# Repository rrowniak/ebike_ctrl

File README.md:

# ebike_ctrl
A small but powerful on-board computer displaying main parameters of almost any electric bike.
It concists of three parts:
* Motherboard - sits close to the BLDC driver and battery. Main responsibility is to gather all needed data like battery voltage, temperatures, current, hall sensor output and so on. The motherboard communicates with UI module via CAN bus.
* Current sensor. This is a hardware module (no firmware needed) connected to the motherboard.
* UI - displays all valuable info to a user. It reads what the motherboard is sending via CAN bus, then interprets the data, does additional calculations and displays on EA DOGXL240W-7 (240x128 pixel COG LCD).

## Features

* Displays current up to +/- 100A, voltage up to 100V and battery percentage

* Current speed, distance traveled (three profiles)

* Consumption in Wh, Wh/km +gain from regenerative charging

* Temperatures: ambient, motor, battery, driver

* Allows for changing views

* and more

## Requirements and dependencies

* GNU Arm Embedded Toolchain

* [l_rr library](https://github.com/rrowniak/l_rr)

## License

Copyright (c) 2020 Rafal Rowniak rrowniak.com

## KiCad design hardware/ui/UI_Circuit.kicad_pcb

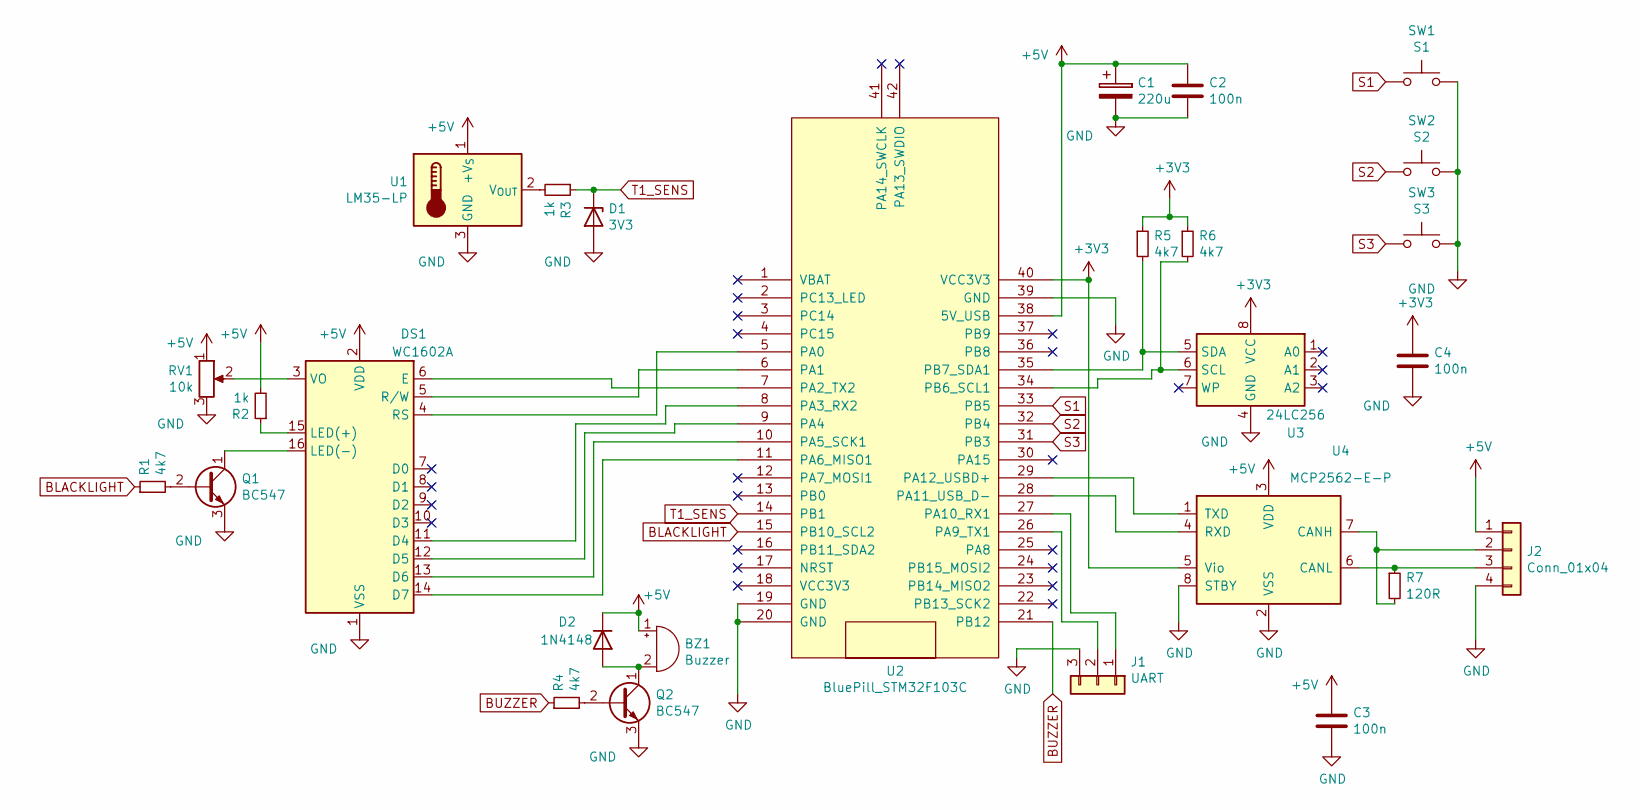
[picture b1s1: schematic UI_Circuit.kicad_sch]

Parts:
BZ1: Buzzer; Buzzer_15x7.5RM7.6
C1: 220u; CP_Radial_D10.0mm_P5.00mm
C2, C3, C4: 100n; C_1206_3216Metric
D1: 3V3; D_1206_3216Metric
D2: 1N4148; D_DO-35_SOD27_P7.62mm_Horizontal
DS1: WC1602A
J1: UART; PinHeader_1x03_P2.54mm_Vertical
J2: Conn_01x04; JST_EH_B4B-EH-A_1x04_P2.50mm_Vertical
Q1, Q2: BC547; TO-92_HandSolder
R1, R4, R5, R6: 4k7; R_1206_3216Metric
R2, R3: 1k; R_1206_3216Metric
R7: 120R; R_Axial_DIN0207_L6.3mm_D2.5mm_P10.16mm_Horizontal
RV1: 10k; Potentiometer_Piher_PT-6-V_Vertical
SW1: S1; SW_PUSH_6mm_H8mm
SW2: S2; SW_PUSH_6mm_H8mm
SW3: S3; SW_PUSH_6mm_H8mm
U1: LM35-LP; TO-92L_HandSolder
U2: BluePill_STM32F103C
U3: 24LC256; DIP-8_W7.62mm
U4: MCP2562-E-P; DIP-8_W7.62mm

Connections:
+3V3: C4.1, R5.1, R6.1, U2.40 (VCC3V3), U3.8 (VCC), U4.5 (Vio)
+5V: BZ1.1 (+), C1.1, C2.1, C3.1, D2.1 (K), DS1.2 (VDD), J2.1, R2.2, RV1.1, U1.1 (+V_{S}), U2.38 (5V_USB), U4.3 (VDD)
BLACKLIGHT: R1.1, U2.15 (PB10_SCL2)
BUZZER: R4.1, U2.21 (PB12)
GND: C1.2, C2.2, C3.2, C4.2, D1.2 (A), DS1.1 (VSS), J1.3, J2.4, Q1.3 (E), Q2.3 (E), RV1.3, SW1.2, SW2.2, SW3.2, U1.3 (GND), U2.19 (GND), U2.20 (GND), U2.39 (GND), U3.4 (GND), U4.2 (VSS), U4.8 (STBY)
unnamed: BZ1.2 (-), D2.2 (A), Q2.1 (C)
unnamed: DS1.3 (VO), RV1.2
unnamed: DS1.4 (RS), U2.5 (PA0)
unnamed: DS1.5 (R/W), U2.6 (PA1)
unnamed: DS1.6 (E), U2.7 (PA2_TX2)
unnamed: DS1.11 (D4), U2.8 (PA3_RX2)
unnamed: DS1.12 (D5), U2.9 (PA4)
unnamed: DS1.13 (D6), U2.10 (PA5_SCK1)
unnamed: DS1.14 (D7), U2.11 (PA6_MISO1)
unnamed: DS1.15 (LED(+)), R2.1
unnamed: DS1.16 (LED(-)), Q1.1 (C)
unnamed: J1.1, U2.27 (PA10_RX1)
unnamed: J1.2, U2.26 (PA9_TX1)
unnamed: J2.2, R7.2, U4.7 (CANH)
unnamed: J2.3, R7.1, U4.6 (CANL)
unnamed: Q1.2 (B), R1.2
unnamed: Q2.2 (B), R4.2
unnamed: R3.2, U1.2 (V_{OUT})
unnamed: R5.2, U2.35 (PB7_SDA1), U3.5 (SDA)
unnamed: R6.2, U2.34 (PB6_SCL1), U3.6 (SCL)
unnamed: U2.28 (PA11_USB_D-), U4.4 (RXD)
unnamed: U2.29 (PA12_USBD+), U4.1 (TXD)
S1: SW1.1, U2.33 (PB5)
S2: SW2.1, U2.32 (PB4)
S3: SW3.1, U2.31 (PB3)
T1_SENS: D1.1 (K), R3.1, U2.14 (PB1)

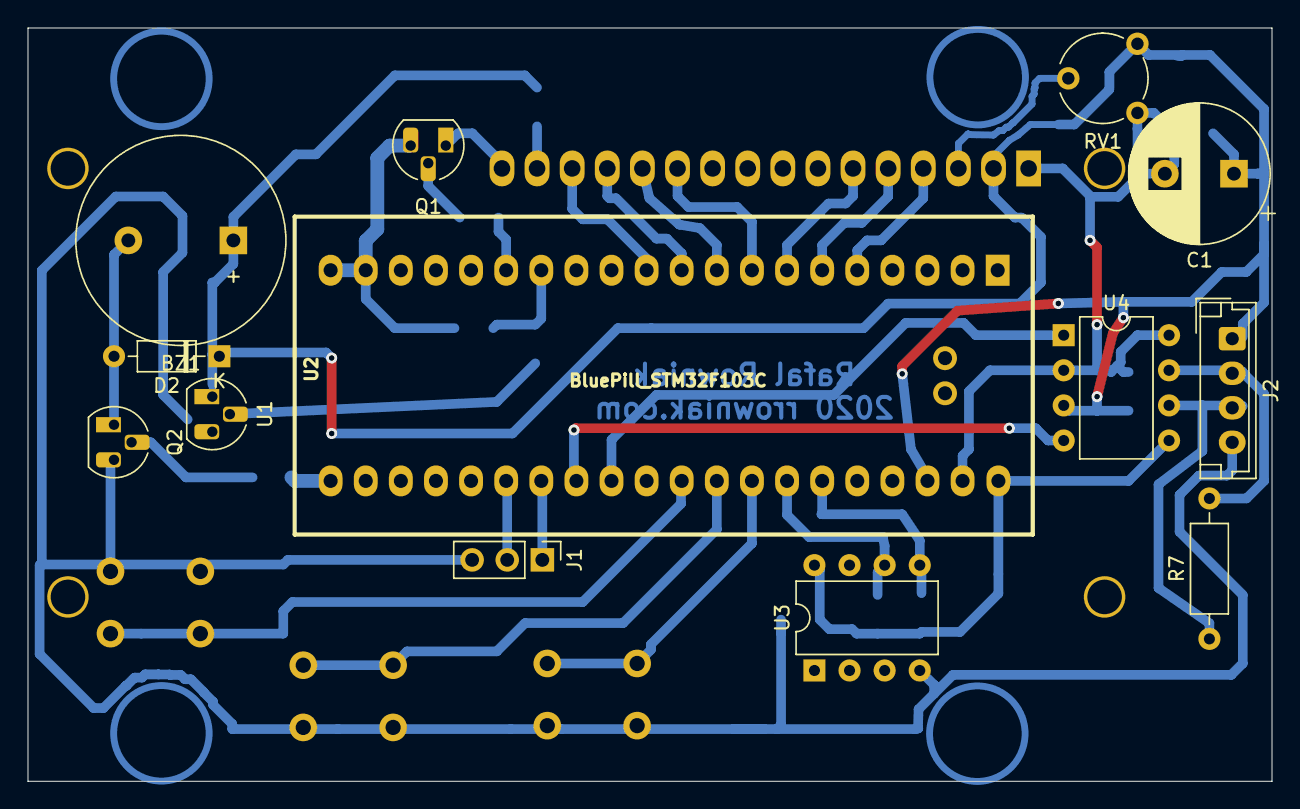
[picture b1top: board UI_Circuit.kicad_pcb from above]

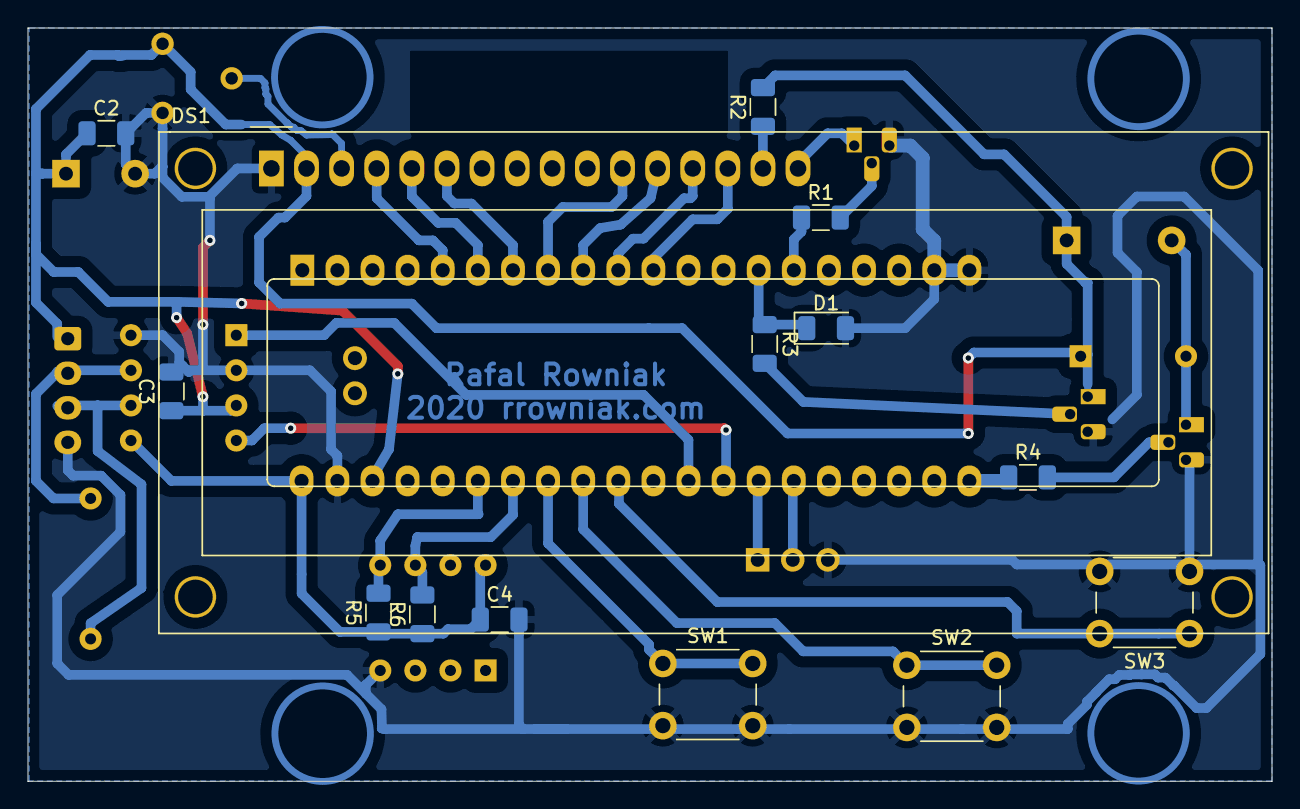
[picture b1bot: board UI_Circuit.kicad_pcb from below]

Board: 2 copper layers, 90.0 x 54.5 mm, 27 parts (14 on the bottom side), 31 nets.

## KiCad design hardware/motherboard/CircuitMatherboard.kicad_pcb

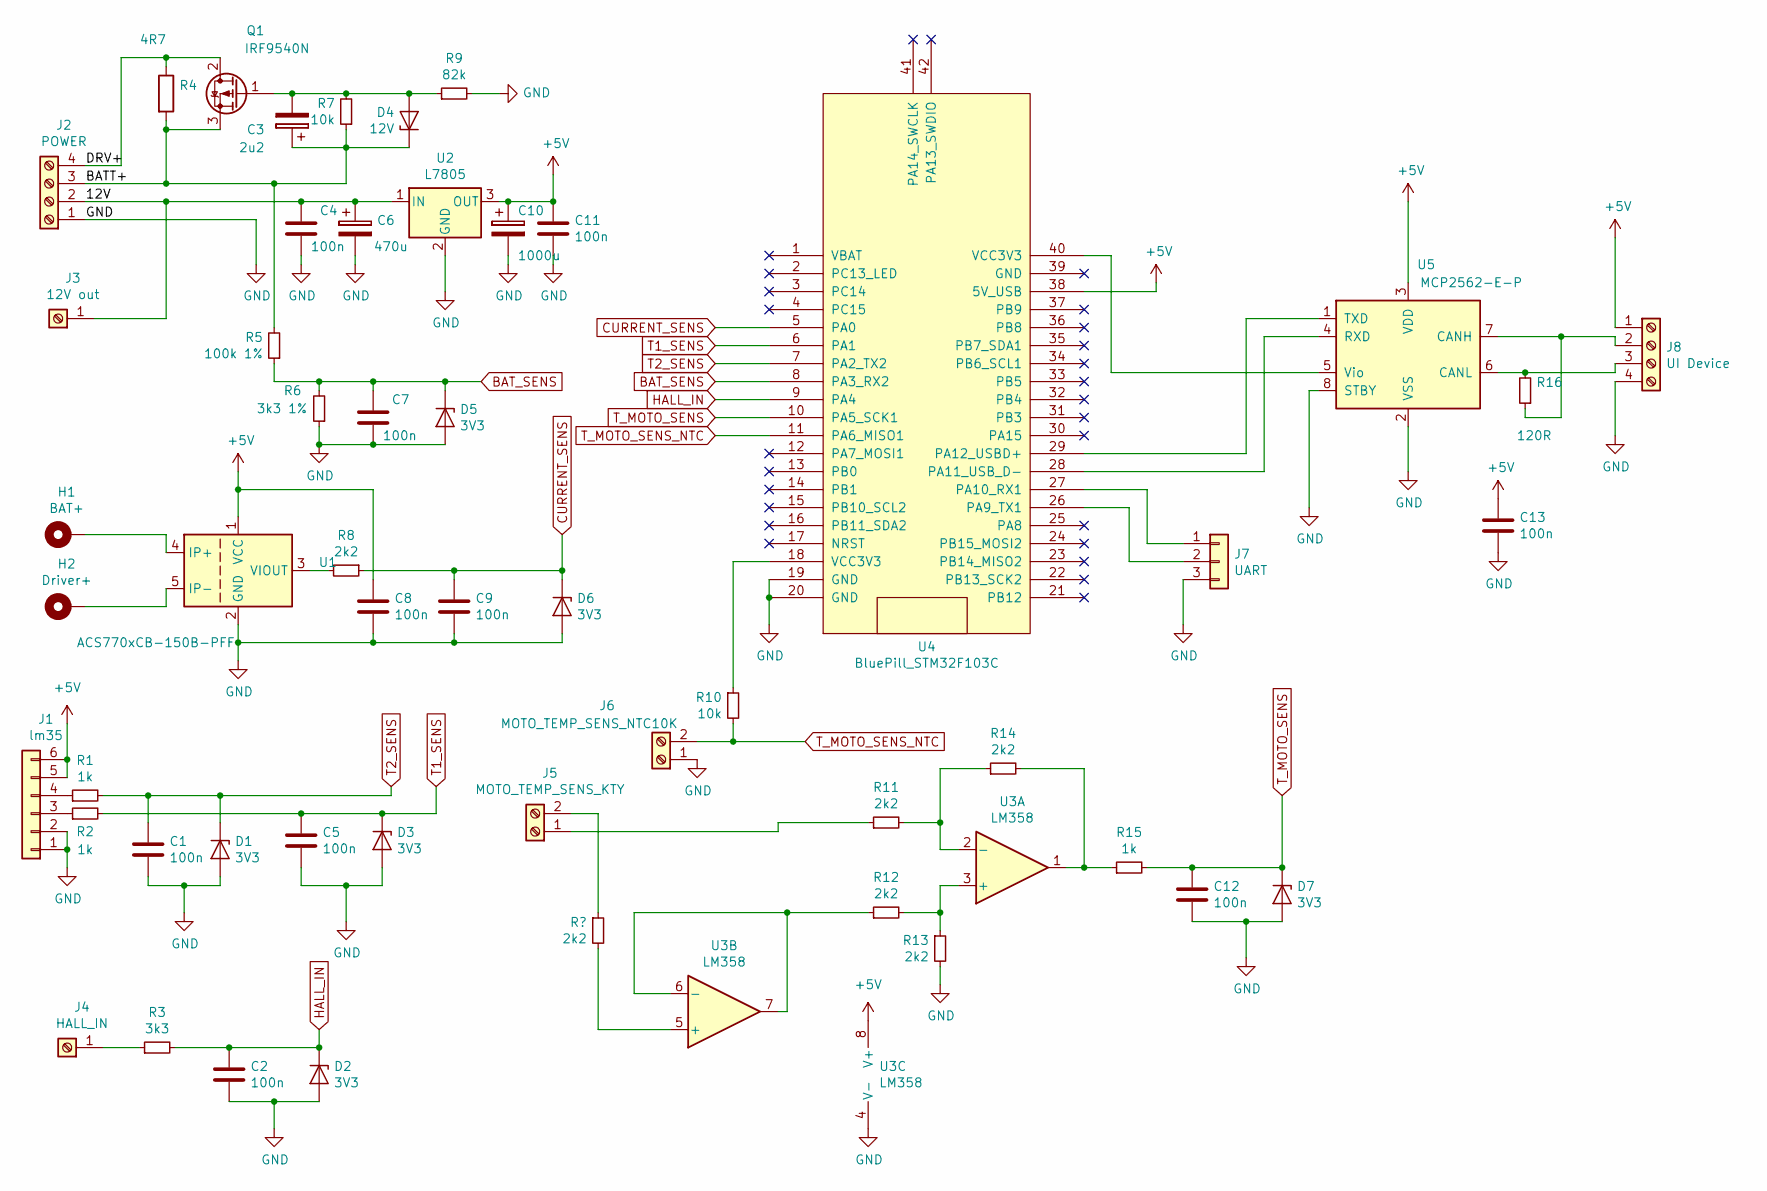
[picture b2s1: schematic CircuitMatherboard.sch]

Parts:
C1: 100n; C_1206_3216Metric
C2, C5, C7, C8, C9, C12, C13: 100n; C_1206_3216Metric_Pad1.42x1.75mm_HandSolder
C3: 2u2; CP_Radial_D5.0mm_P2.50mm
C4, C11: 100n; C_Disc_D4.3mm_W1.9mm_P5.00mm
C6: 470u; CP_Radial_D10.0mm_P5.00mm
C10: 1000u; CP_Radial_D10.0mm_P5.00mm
D1, D2, D3, D5, D6, D7: 3V3; D_1206_3216Metric
D4: 12V; D_1206_3216Metric
H1: BAT+; MountingHole_8.4mm_M8_Pad
H2: Driver+; MountingHole_8.4mm_M8_Pad
J1: lm35; JST_EH_B6B-EH-A_1x06_P2.50mm_Vertical
J2: POWER; SolderWirePad_1x04_P5.08mm_Drill1.5mm
J3: 12V out; SolderWirePad_1x01_Drill1.5mm
J4: HALL_IN; SolderWirePad_1x01_Drill0.8mm
J5: MOTO_TEMP_SENS_KTY; JST_EH_B2B-EH-A_1x02_P2.50mm_Vertical
J6: MOTO_TEMP_SENS_NTC10K; JST_EH_B2B-EH-A_1x02_P2.50mm_Vertical
J7: UART; JST_EH_B3B-EH-A_1x03_P2.50mm_Vertical
J8: UI Device; JST_EH_B4B-EH-A_1x04_P2.50mm_Vertical
Q1: IRF9540N; TO-220-3_Vertical
R1, R2: 1k; R_1206_3216Metric
R3: 3k3; R_1206_3216Metric
R4: 4R7; R_Axial_Power_L25.0mm_W9.0mm_P30.48mm
R5: 100k 1%; R_Axial_DIN0207_L6.3mm_D2.5mm_P10.16mm_Horizontal
R6: 3k3 1%; R_Axial_DIN0207_L6.3mm_D2.5mm_P10.16mm_Horizontal
R7, R10: 10k; R_1206_3216Metric
R8, R12, R13: 2k2; R_Axial_DIN0207_L6.3mm_D2.5mm_P10.16mm_Horizontal
R9: 82k; R_Axial_DIN0207_L6.3mm_D2.5mm_P10.16mm_Horizontal
R11, R14: 2k2; R_1206_3216Metric
R15: 1k; R_Axial_DIN0207_L6.3mm_D2.5mm_P10.16mm_Horizontal
R16: 120R; R_Axial_DIN0207_L6.3mm_D2.5mm_P10.16mm_Horizontal
U1: ACS770xCB-150B-PFF; Allegro_CB_PFF
U2: L7805; TO-220-3_Vertical
U3: LM358; DIP-8_W7.62mm
U4: BluePill_STM32F103C
U5: MCP2562-E-P; DIP-8_W7.62mm

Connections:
+5V: C8.1, C10.1, C11.1, C13.1, J1.5, J1.6, J8.1, U1.1 (VCC), U2.3 (OUT), U3.8 (V+), U4.38 (5V_USB), U5.3 (VDD)
/12V: C4.1, C6.1, J2.2, J3.1, U2.1 (IN)
/BATT+: C3.1, D4.1 (K), J2.3, Q1.3 (S), R4.2, R5.2, R7.1
/DRV+: J2.4, Q1.2 (D), R4.1
BAT_SENS: C7.1, D5.1 (K), R5.1, R6.2, U4.8 (PA3_RX2)
CURRENT_SENS: C9.1, D6.1 (K), R8.1, U4.5 (PA0)
GND: C1.2, C2.2, C4.2, C5.2, C6.2, C7.2, C8.2, C9.2, C10.2, C11.2, C12.2, C13.2, D1.2 (A), D2.2 (A), D3.2 (A), D5.2 (A), D6.2 (A), D7.2 (A), J1.1, J1.2, J2.1, J6.1, J7.3, J8.4, R6.1, R9.2, R13.2, U1.2 (GND), U2.2 (GND), U3.4 (V-), U4.19 (GND), U4.20 (GND), U5.2 (VSS), U5.8 (STBY)
HALL_IN: C2.1, D2.1 (K), R3.2, U4.9 (PA4)
unnamed: C3.2, D4.2 (A), Q1.1 (G), R7.2, R9.1
unnamed: H1.1, U1.4 (IP+)
unnamed: H2.1, U1.5 (IP-)
unnamed: J1.3, R2.1
unnamed: J1.4, R1.1
unnamed: J4.1, R3.1
unnamed: J5.1, R11.1
unnamed: J5.2, U3.5 (+)
unnamed: J7.1, U4.27 (PA10_RX1)
unnamed: J7.2, U4.26 (PA9_TX1)
unnamed: J8.2, R16.1, U5.7 (CANH)
unnamed: J8.3, R16.2, U5.6 (CANL)
unnamed: R8.2, U1.3 (VIOUT)
unnamed: R10.1, U4.18 (VCC3V3)
unnamed: R11.2, R14.1, U3.2 (-)
unnamed: R12.1, U3.6 (-), U3.7
unnamed: R12.2, R13.1, U3.3 (+)
unnamed: R14.2, R15.1, U3.1
unnamed: U4.28 (PA11_USB_D-), U5.4 (RXD)
unnamed: U4.29 (PA12_USBD+), U5.1 (TXD)
unnamed: U4.40 (VCC3V3), U5.5 (Vio)
T1_SENS: C5.1, D3.1 (K), R2.2, U4.6 (PA1)
T2_SENS: C1.1, D1.1 (K), R1.2, U4.7 (PA2_TX2)
T_MOTO_SENS: C12.1, D7.1 (K), R15.2, U4.10 (PA5_SCK1)
T_MOTO_SENS_NTC: J6.2, R10.2, U4.11 (PA6_MISO1)

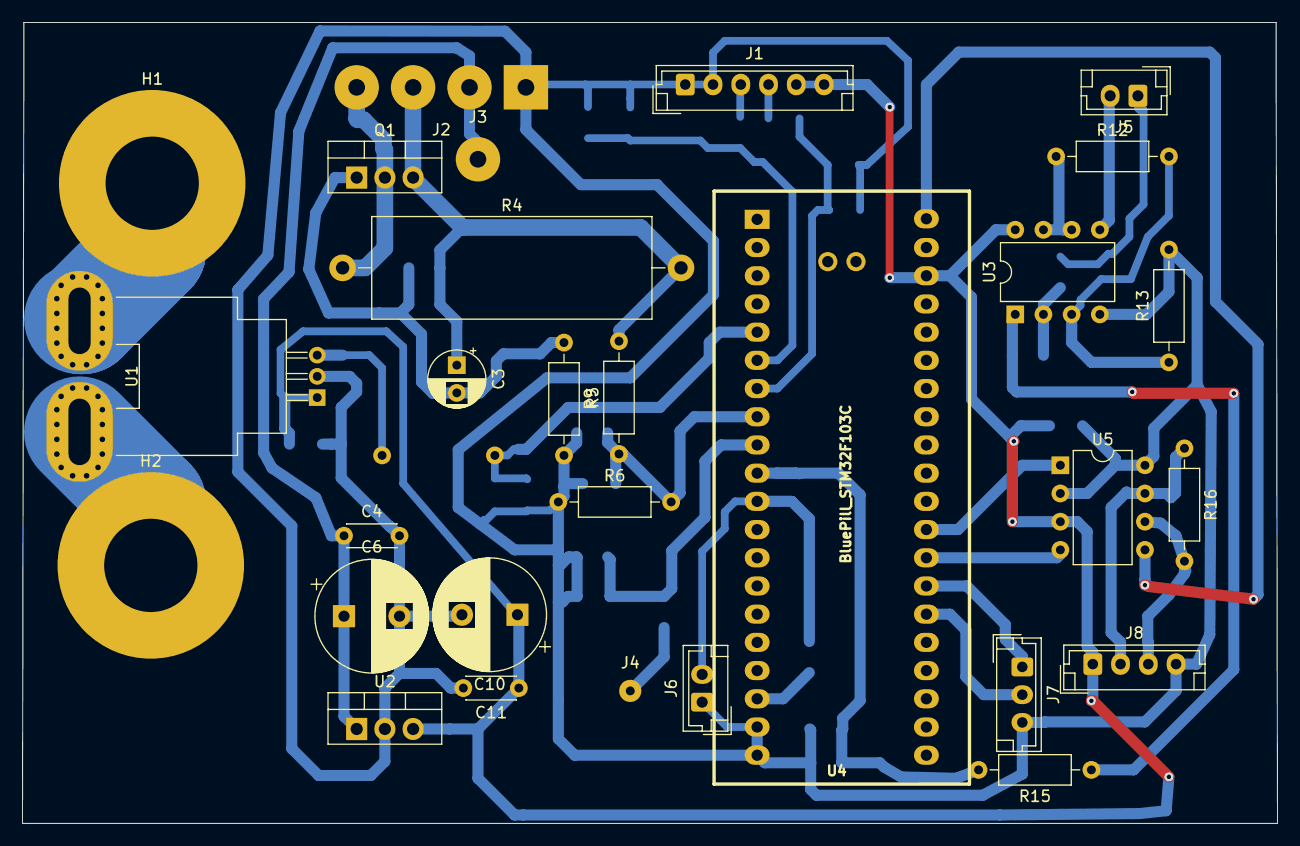
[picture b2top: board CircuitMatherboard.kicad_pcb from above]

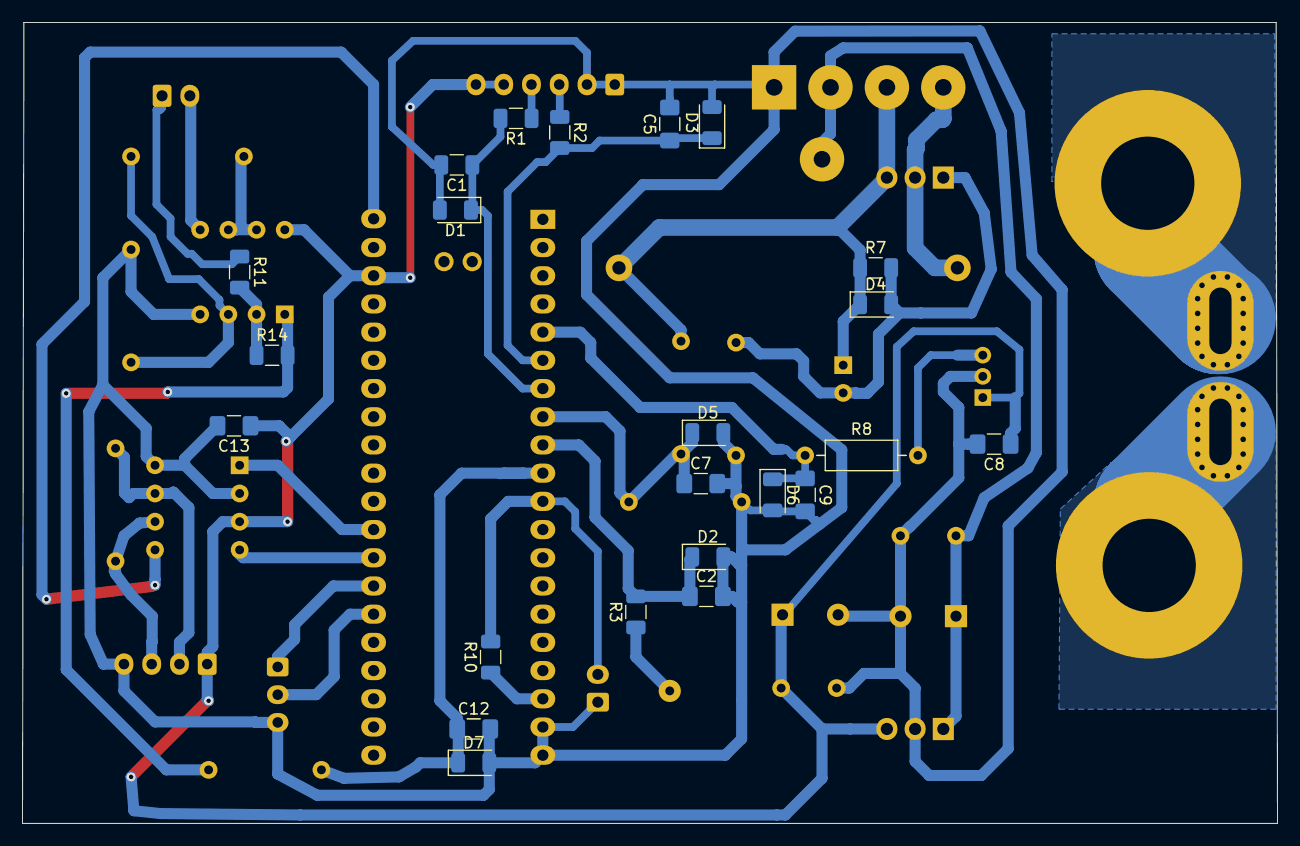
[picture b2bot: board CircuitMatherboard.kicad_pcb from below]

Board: 2 copper layers, 113.0 x 72.1 mm, 52 parts (23 on the bottom side), 33 nets.

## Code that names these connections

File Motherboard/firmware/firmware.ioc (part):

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Mcu.UserName=STM32F103C8Tx
PA11.Mode=Master
PA3.GPIOParameters=GPIO_Label
PA6.GPIO_Label=T4_SENS
PA2.GPIOParameters=GPIO_Label
PC15-OSC32_OUT.GPIO_Label=LIGHTS
RCC.SYSCLKSource=RCC_SYSCLKSOURCE_PLLCLK
PD1-OSC_OUT.Signal=RCC_OSC_OUT
PA12.Signal=CAN_TX
PA0-WKUP.GPIOParameters=GPIO_Label
PA1.GPIOParameters=GPIO_Label
Mcu.Package=LQFP48
PA6.Signal=ADCx_IN6
PA2.GPIO_Label=T2_SENS
PA10.Signal=USART1_RX
PA5.GPIOParameters=GPIO_Label
PC15-OSC32_OUT.GPIOParameters=GPIO_Label
PA4.GPIO_Label=HALL_IN
PA3.Signal=ADCx_IN3
PA6.GPIOParameters=GPIO_Label
PD1-OSC_OUT.Mode=HSE-External-Oscillator
PA10.Mode=Asynchronous
PD0-OSC_IN.Signal=RCC_OSC_IN
PA0-WKUP.GPIO_Label=CURRENT_SENS
PA0-WKUP.Signal=ADCx_IN0
PA9.Mode=Asynchronous
PA9.Signal=USART1_TX
PC15-OSC32_OUT.Signal=GPIO_Output
PA1.Signal=ADCx_IN1
PD0-OSC_IN.Mode=HSE-External-Oscillator
PA5.Signal=ADCx_IN5
board=custom
PA1.GPIO_Label=T1_SENS
PA4.GPIOParameters=GPIO_Label
Mcu.Name=STM32F103C(8-B)Tx
PA2.Signal=ADCx_IN2
PA4.Signal=GPXTI4
RCC.SYSCLKFreq_VALUE=72000000
PA12.Mode=Master
PA5.GPIO_Label=T3_SENS
PA11.Signal=CAN_RX
PA3.GPIO_Label=BAT_SENS

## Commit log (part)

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2020-10-12 Readme updated
2022-03-08 Display km overflow error fixed
2022-03-21 Bug fixing (rounding errors, temperature sensor issues, etc)
2022-03-21 Removed accidentally added files
